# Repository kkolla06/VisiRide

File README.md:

# VisiRide - 10-cloudcrackers
---
Smart 2FA system for electric scooter rentals

## Project structure

### Hardware Component
Located in `embedded/`
* `embedded/breakout/breakout/breakout_pcb/` contains breakout PCB for GPS, LTE, Camera (including Gerber files) developed in KiCAD V5 (https://www.kicad.org/download/)
* `embedded/` contains associated Quartus project files to build hardware system for DE1-SoC along with top level `on_board_computer.sv` to instantiate platform designer system on device
* `embedded/software/on_board_computer/dev/` contains firmware stack written from scratch for project
* `embedded/software/on_board_computer/FreeRTOS` contains FreeRTOS source code and port
* `embedded/software/on_board_computer/` contains makefiles, main, project files etc

DE1-SoC system was built using Quartus version 18.1 and embedded software compiled with included NIOS II build tools. 

### Cloud Server 
* The server is entirely contained in server.js
* facial_recognition library source: https://github.com/ageitgey/face_recognition

Written in Node.js 

### User Application 
Located in `dart/`
* `dart/lib/` is all written from scratch.
  * `dart/lib/api/` contains all the code required for facilitating api calls to the server using the http package.
  * `dart/lib/model/` contains custom dart objects for scooter and users.
  * `dart/lib/pages/` contains the different pages the user can interact with.
    * `dart/lib/pages/MapPage.dart` contains the map interface, provided by [Google Maps](https://developers.google.com/maps/), and contains the code to periodically update server with the user's current location grab the list of scooters.
    * `dart/lib/pages/Signup.dart` features an [image cropper provided by Yalantis](https://github.com/Yalantis/uCrop).
  * `dart/lib/utils/` contains classes to store some helper functions for the image picker and getting user data.
  * `dart/lib/widget/` contains custom flutter widgets
 * `dart/pubspec.yaml` contains all the imported [packages](https://pub.dev/) used, some are open-source, the others are written by the Flutter team.
 
 Apks were all built using Flutter in Android Studio.

### Cloud Database 
* Endpoints for modifying the database are defined in `server.js`
* MondoDB database is deployed on the cloud via an Azure VM

Written in Node.js

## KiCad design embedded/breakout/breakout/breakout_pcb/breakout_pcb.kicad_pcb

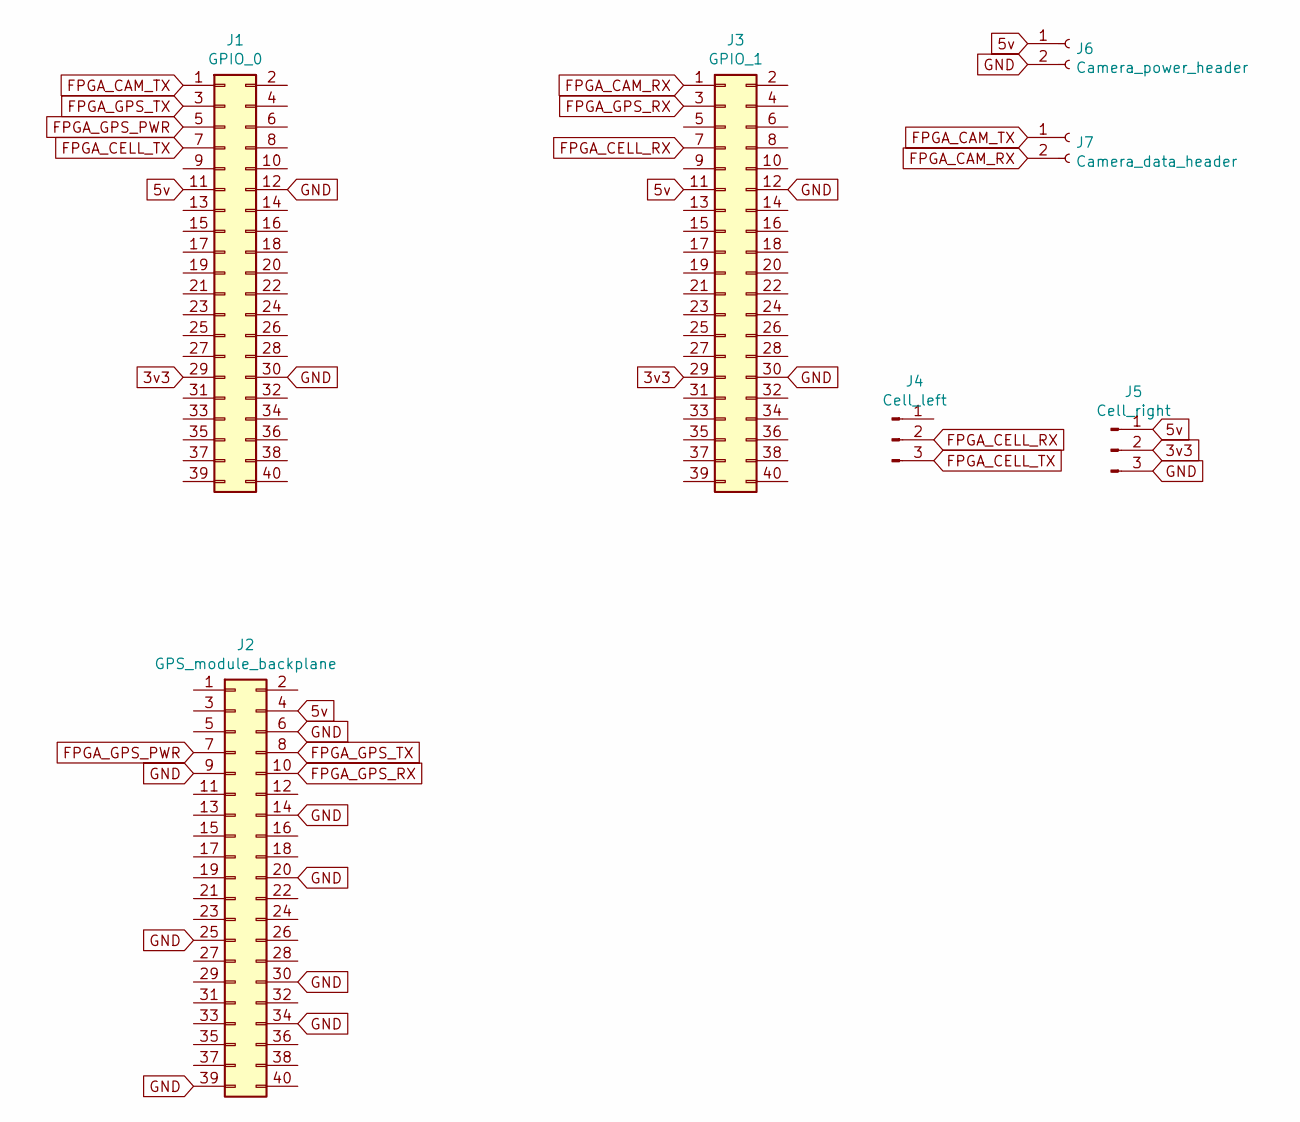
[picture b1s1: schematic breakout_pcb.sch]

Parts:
J1: GPIO_0; PinHeader_2x20_P2.54mm_Vertical
J2: GPS_module_backplane; 3020-40-0100-00
J3: GPIO_1; PinHeader_2x20_P2.54mm_Vertical
J4: Cell_left; PinHeader_1x03_P2.54mm_Vertical
J5: Cell_right; PinHeader_1x03_P2.54mm_Vertical
J6: Camera_power_header; 691214110002
J7: Camera_data_header; 691214110002

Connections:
3v3: J1.29, J3.29, J5.2
5v: J1.11, J2.4, J3.11, J5.1, J6.1
FPGA_CAM_RX: J3.1, J7.2
FPGA_CAM_TX: J1.1, J7.1
FPGA_CELL_RX: J3.7, J4.2
FPGA_CELL_TX: J1.7, J4.3
FPGA_GPS_PWR: J1.5, J2.7
FPGA_GPS_RX: J2.10, J3.3
FPGA_GPS_TX: J1.3, J2.8
GND: J1.12, J1.30, J2.6, J2.9, J2.14, J2.20, J2.25, J2.30, J2.34, J2.39, J3.12, J3.30, J5.3, J6.2

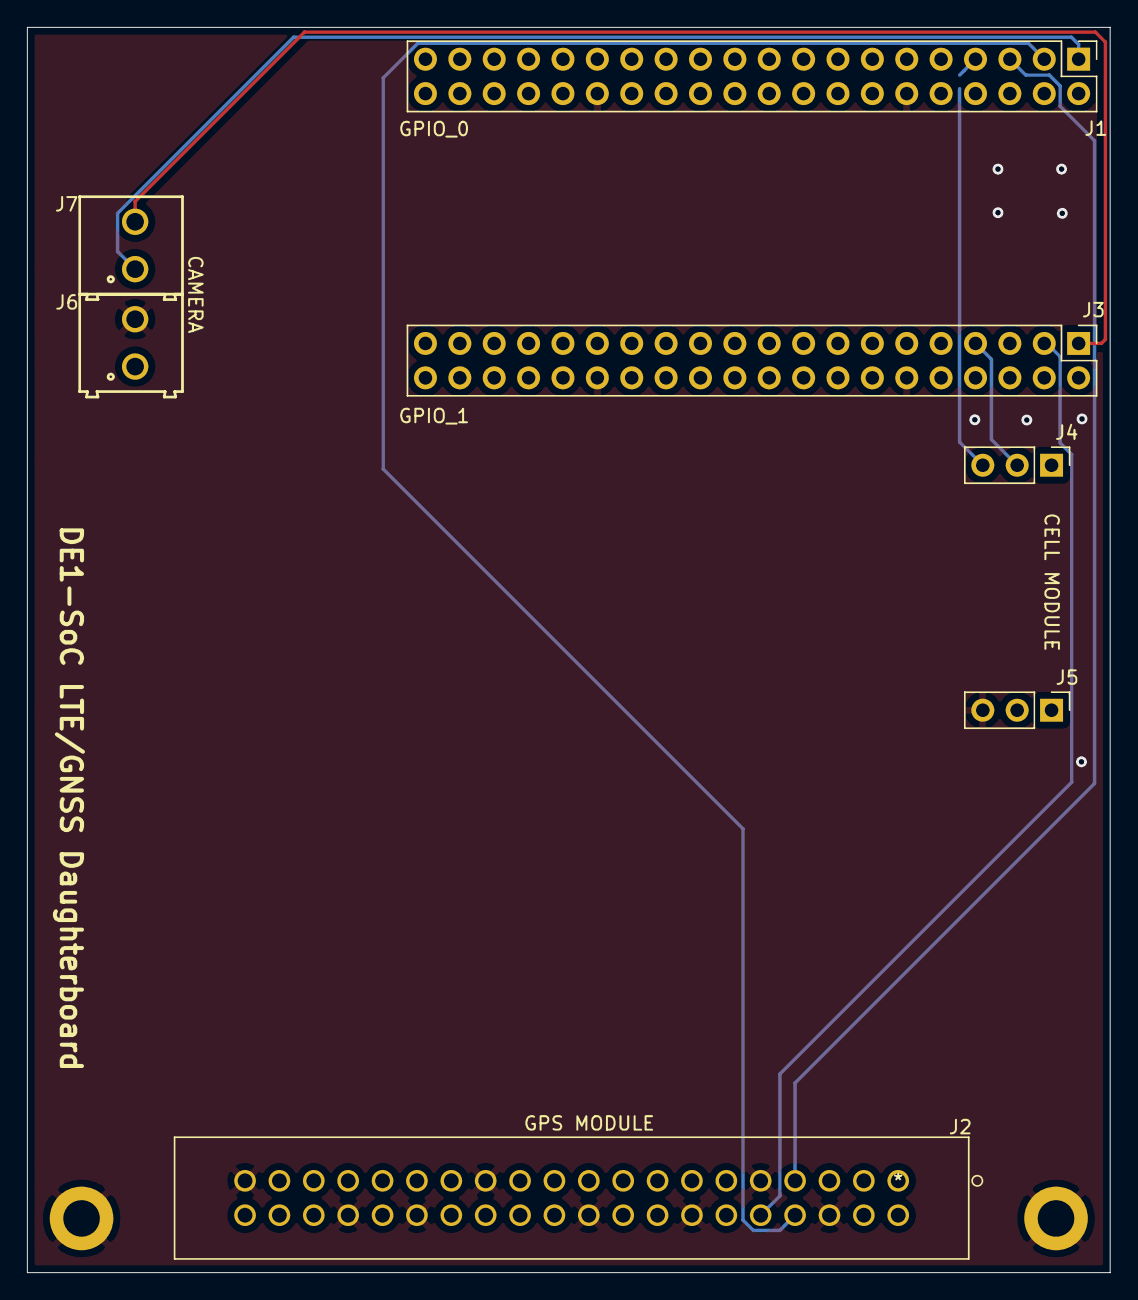
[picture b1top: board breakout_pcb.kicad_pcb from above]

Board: 4 copper layers, 80.0 x 92.0 mm, 7 parts (0 on the bottom side), 10 nets.

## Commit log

2023-05-02 VisiRide Public

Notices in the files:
parts and their libraries:
Copyright 2021 Accelerated Designs. All rights reserved.
